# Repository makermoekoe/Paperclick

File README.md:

# Paperclick

</a>

Paperclick is a simple device which combines a [Picoclick-C3T](https://github.com/makermoekoe/Picoclick-C3) with the smallest EPaper display I found in the internet: [a 1.02" 128x80 pixels EPD](https://www.waveshare.com/wiki/1.02inch_e-Paper_Module). The initial task was to create a simple activity tracker which updates the EPaper display with the current date and time once the display is pressed (actually it is not the display sensing the press, it's a button behind the display). The device gets the time from an NTP server over WiFi. Additionally the device can update an online service with the date/time the Paperclick was pressed.

Paperclick is based on the single core ESP32-C3 processor which is used in the Picoclick C3T as well. Furthermore it comes with an optimized battery monitoring which brings the complete device down to around 200nA current consumption in idle state.
The latching circuit is optimized as well - it now doesn't use a GPIO of the MCU as a latch like it was done before, it uses the power supply of the embedded flash. Once the ESP32 enters deepsleep mode, that voltage supply will be pulled low to save a bit of power. This triggers the latch and the device will be disabled. And the best feature with this is that we don't have to struggle with the initial timings (boot speed up) like it was necessary with the [Picoclick-C3T](https://github.com/makermoekoe/Picoclick-C3) in its first version. The above mentioned power supply pin is immediately high once the MCU gets power (~3ms compared to minimal 60ms with using a GPIO). This makes it possible to use the Arduino framework without any restrictions!

## Features

- ESP32-C3 MCU with chip antenna
- 1.02" 128x80 pixel Epaper display
- Onboard battery charger
- Optimized battery capacity estimation
- Simple One-Button user interface (Two optional buttons available)
- WS2812 user LED
- LiPo battery charger with indicator LED

The [Youtube video](https://www.youtube.com/watch?v=tOb_UypiWvQ) shows the assembly and soldering process, explains how the battery monitoring works and shows this little thing in action.

## Battery monitoring

</a>

Till now I have estimated the battery capacity with a simple voltage divider between VBAT and GND and an analog input of the MCU to read the voltage. This will draw current all the time, even if the device is not activated.

```
I = V / R = 4V / (1MΩ + 250kΩ) = 3,2µA
I = V / R = 4V / (250kΩ + 250kΩ) = 8µA
```

In order to save these few µA of current, I searched for other solution which lead me to [this](https://jeelabs.org/2013/05/18/zero-power-measurement-part-2/index.html#comments) article by Jean-Claude Wippler, where he additionally used a mosfet, a resistor and a capacitor to create something like a one-shot trigger for the voltage divider.

After some test with a Picoclick and my scope, that solution seems to be a very cool and interesting one. Paperclick is the first board where I tried this circuit, that's why there are so many measurement test points.

## Power consumption

</a>

- 82mA in average while WiFi connecting/transmitting and updating the ePaper display
- 38mA in average with WiFi disabled and updating the ePaper display
- 140nA in average in idle state

## Assembled devive

</a>

</a>

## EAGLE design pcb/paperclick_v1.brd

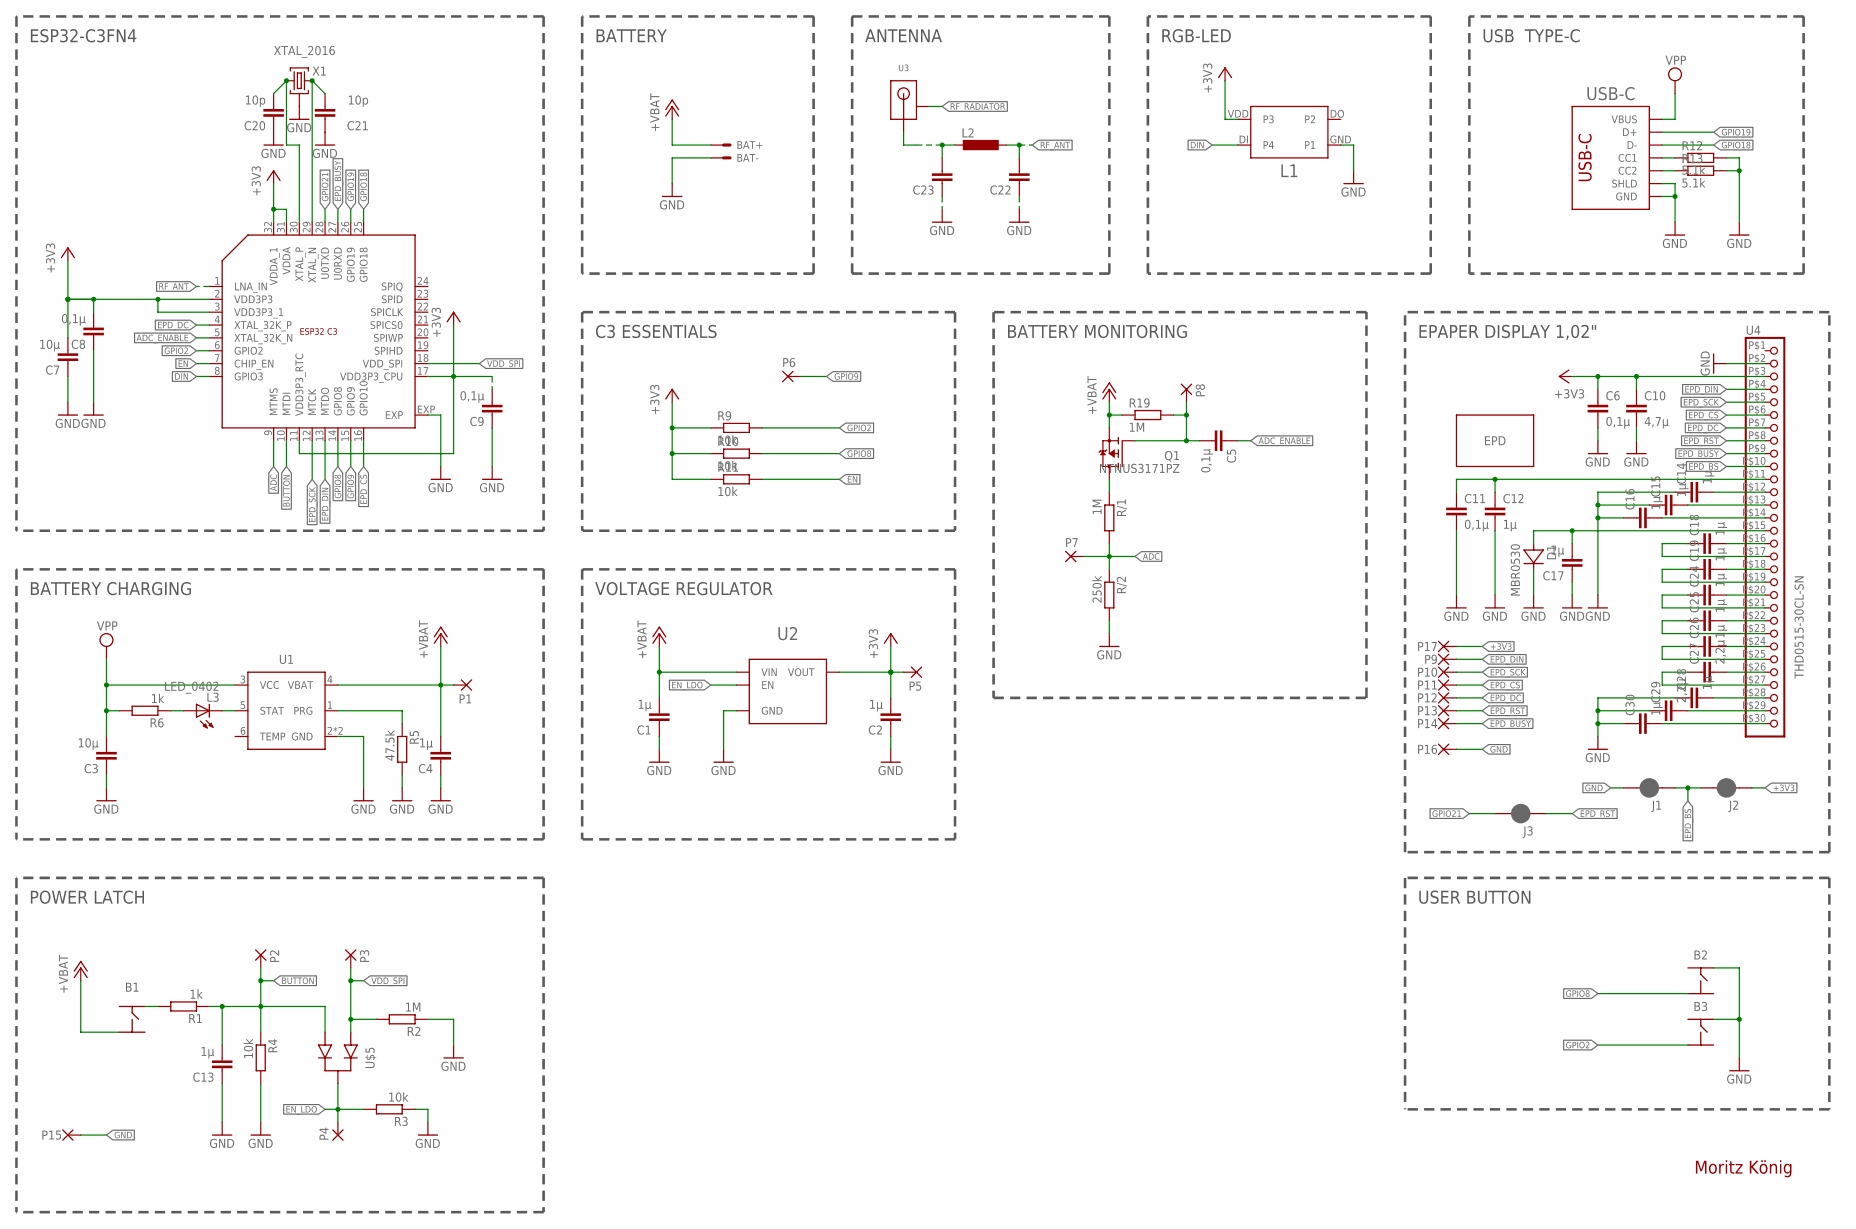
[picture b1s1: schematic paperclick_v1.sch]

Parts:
B1: BUTTON_4PIN_TS-1070A; BUTTON_WHITE_SMD
B2, B3: PTS840ESDGMSMTRLFS
BAT+: TP/SP-1.5X1.0; SOLDERPAD_1.5X1.0
BAT-: TP/SP-1.5X1.0; SOLDERPAD_1.5X1.0
C1, C2, C4, C12, C13, C14, C15, C16, C17, C18, C19, C24, C25, C26, C28, C30: 1µ; C0402_S
C3, C7: 10µ; C0402_S
C5, C6, C8, C9, C11: 0,1µ; C0402_S
C10: 4,7µ; C0402_S
C20, C21: 10p; C0402_S
C22, C23: C0201
C27, C29: 2,2µ; C0402_S
D1: MBR0530; SOD123
ESP1: ESP32_C3_QFN32; QFN32
J1, J2, J3: SMT_JUMPER_2_NC_PASTE; JUMPER_SMALL
L1: WS2812_2020
L2: L0201
L3: LED_0402; CHIPLED_0402
P1, P2, P3, P4, P5, P6, P7, P8, P9, P10, P11, P12, P13, P14, P15, P16, P17: SMD-R1
Q1: NTNUS3171PZ; SOT1123
R1, R6: 1k; R0402
R2, R19: 1M; R0402
R3, R4, R9, R10, R11: 10k; R0402
R5: 47.5k; R0402
R12, R13: 5.1k; R0402
R/1: 1M; R0402
R/2: 250k; R0402
U1: WS4518D; DFN-6
U2: MIC5504; TDFN4
U3: ANT016008LCS2442MA2
U4: THD0515-30CL-SN
U$2: EPD-102-30PIN-TW
U$5: DAN222; SOT523
USB-C: USB_C_C393939; USBC_C393939
X1: XTAL_2016

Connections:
+3V3: C2.P$2 (2), C6.P$1 (1), C7.P$2 (2), C8.P$2 (2), C9.P$2 (2), C10.P$1 (1), ESP1.2 (VDD3P3), ESP1.3 (VDD3P3_1), ESP1.11 (VDD3P3_RTC), ESP1.17 (VDD3P3_CPU), ESP1.31 (VDDA), ESP1.32 (VDDA_1), J2.P$1 (1), L1.VDD (P3), P5.P$1, P17.P$1, R9.1, R10.1, R11.1, U2.P1 (VOUT), U4.P$3 (3)
+VBAT: B1.P$2 (3), BAT+.1, C1.P$2 (2), C4.P$2 (2), P1.P$1, Q1.2 (S), R19.1, U1.4 (VBAT), U2.P4 (VIN)
ADC: ESP1.9 (MTMS), P7.P$1, R/1.2, R/2.1
ADC_ENABLE: C5.P$1 (1), ESP1.5 (XTAL_32K_N)
BUTTON: C13.P$2 (2), ESP1.10 (MTDI), P2.P$1, R1.1, R4.1, U$5.2
DIN: ESP1.8 (GPIO3), L1.DI (P4)
EN: ESP1.7 (CHIP_EN), R11.2
EN_LDO: P4.P$1, R3.2, U2.P3 (EN), U$5.3
EPD_BS: J1.P$1 (1), J2.P$2 (2), U4.P$10 (10)
EPD_BUSY: ESP1.27 (U0RXD), P14.P$1, U4.P$9 (9)
EPD_CS: ESP1.16 (GPIO10), P11.P$1, U4.P$6 (6)
EPD_DC: ESP1.4 (XTAL_32K_P), P12.P$1, U4.P$7 (7)
EPD_DIN: ESP1.13 (MTDO), P9.P$1, U4.P$4 (4)
EPD_RST: J3.P$1 (1), P13.P$1, U4.P$8 (8)
EPD_SCK: ESP1.12 (MTCK), P10.P$1, U4.P$5 (5)
GND: B2.2, B3.2, BAT-.1, C1.P$1 (1), C2.P$1 (1), C3.P$1 (1), C4.P$1 (1), C6.P$2 (2), C7.P$1 (1), C8.P$1 (1), C9.P$1 (1), C10.P$2 (2), C11.P$2 (2), C12.P$2 (2), C13.P$1 (1), C14.P$1 (1), C15.P$1 (1), C16.P$1 (1), C17.P$1 (1), C20.P$1 (1), C21.P$1 (1), C22.P$1 (1), C23.P$1 (1), C28.P$1 (1), C29.P$1 (1), C30.P$1 (1), D1.P$2 (C), ESP1.EXP, J1.P$2 (2), L1.GND (P1), P15.P$1, P16.P$1, R2.1, R3.1, R4.2, R5.2, R12.2, R13.2, R/2.2, U1.2 (GND), U1.EXP (GND), U2.EXP (GND), U2.P2 (GND), U4.P$2 (2), USB-C.A1B12 (GND), USB-C.B1A12 (GND), USB-C.S1 (SHLD), USB-C.S2 (SHLD), USB-C.S3 (SHLD), USB-C.S4 (SHLD), X1.P2 (G), X1.P4 (G)
GPIO2: B3.3, ESP1.6 (GPIO2), R9.2
GPIO8: B2.3, ESP1.14 (GPIO8), R10.2
GPIO9: ESP1.15 (GPIO9), P6.P$1
GPIO18: ESP1.25 (GPIO18), USB-C.A7 (D-), USB-C.B7 (D-)
GPIO19: ESP1.26 (GPIO19), USB-C.A6 (D+), USB-C.B6 (D+)
GPIO21: ESP1.28 (U0TXD), J3.P$2 (2)
unnamed: B1.P$4 (2), R1.2
unnamed: L3.P$2 (A), R6.1
unnamed: L3.P$1 (C), U1.5 (STAT)
unnamed: Q1.3 (D), R/1.1
unnamed: C23.P$2 (2), L2.P$2 (2), U3.3 (ANT)
unnamed: C5.P$2 (2), P8.P$1, Q1.1 (G), R19.2
unnamed: R13.1, USB-C.B5 (CC2)
unnamed: C11.P$1 (1), C12.P$1 (1), U4.P$11 (11)
unnamed: C14.P$2 (2), U4.P$12 (12)
unnamed: C15.P$2 (2), U4.P$13 (13)
unnamed: C16.P$2 (2), U4.P$14 (14)
unnamed: R5.1, U1.1 (PRG)
unnamed: C17.P$2 (2), D1.P$1 (A), U4.P$15 (15)
unnamed: R12.1, USB-C.A5 (CC1)
unnamed: C20.P$2 (2), ESP1.30 (XTAL_P), X1.P1 (1)
unnamed: C21.P$2 (2), ESP1.29 (XTAL_N), X1.P3 (2)
unnamed: C18.P$2 (2), U4.P$16 (16)
unnamed: C18.P$1 (1), U4.P$17 (17)
unnamed: C19.P$2 (2), U4.P$18 (18)
unnamed: C19.P$1 (1), U4.P$19 (19)
unnamed: C24.P$2 (2), U4.P$20 (20)
unnamed: C24.P$1 (1), U4.P$21 (21)
unnamed: C25.P$2 (2), U4.P$22 (22)
unnamed: C25.P$1 (1), U4.P$23 (23)
unnamed: C26.P$2 (2), U4.P$24 (24)
unnamed: C26.P$1 (1), U4.P$25 (25)
unnamed: C27.P$2 (2), U4.P$26 (26)
unnamed: C27.P$1 (1), U4.P$27 (27)
unnamed: C28.P$2 (2), U4.P$28 (28)
unnamed: C29.P$2 (2), U4.P$29 (29)
unnamed: C30.P$2 (2), U4.P$30 (30)
RF_ANT: C22.P$2 (2), ESP1.1 (LNA_IN), L2.P$1 (1)
RF_RADIATOR: U3.1 (GND)
VDD_SPI: ESP1.18 (VDD_SPI), P3.P$1, R2.2, U$5.1
VPP: C3.P$2 (2), R6.2, U1.3 (VCC), USB-C.A4B9 (VBUS), USB-C.B4A9 (VBUS)

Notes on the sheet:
Moritz König
BATTERY MONITORING
ANTENNA
USB TYPE-C
VOLTAGE REGULATOR
RGB-LED
POWER LATCH
C3 ESSENTIALS
BATTERY CHARGING
ESP32-C3FN4
BATTERY
EPAPER DISPLAY 1,02"
USER BUTTON

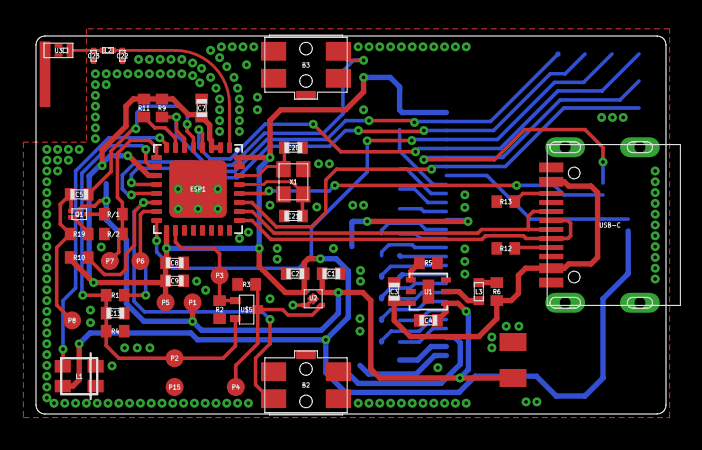
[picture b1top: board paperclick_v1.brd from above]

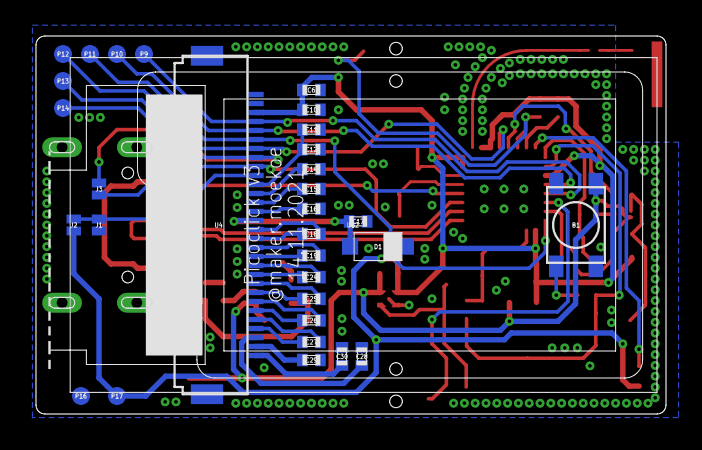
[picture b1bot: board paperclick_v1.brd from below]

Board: 2 copper layers, 35.0 x 21.0 mm, 83 parts (32 on the bottom side), 56 nets.

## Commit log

2022-03-03 added pcb files
2022-04-04 added first code example
2022-04-05 added deepsleep example with VDDSPI
2022-04-07 added tap here example
2022-04-07 added first version case
2022-04-25 added working WiFi and tap example
2022-04-27 updated docs
2022-05-08 updated schematics and docs
2022-05-08 added power consumption to docs
2022-05-09 added pictures
2022-05-12 updated schematics with correct values for the matching network
2022-05-17 added youtube video link
2023-05-28 Fix broken link to waveshare.com
